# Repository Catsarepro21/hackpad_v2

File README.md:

# Macropad
A custom macropad with 6 keys, bluetooth(ESP32-S3), battery, RGB, 2 and rotary encoders. This is my second macropad, because the first one wasn't that good but I still have parts some parts left over from it. 

Files:

[PCB](PCB)

[Case](https://github.com/Catsarepro21/hackpad_v2/blob/main/case)

[Gerbers](PCB/gerbers.zip)

BOM: [BOM.md](BOM.md)

[Onshape](https://cad.onshape.com/documents/e5e00bd96b00b1f98fd3bff8/w/d80bdedc56342f5387c6fe9a/e/f05423852afba8350f5d5474?renderMode=0&uiState=6ad917cca941be13c57e1d41)

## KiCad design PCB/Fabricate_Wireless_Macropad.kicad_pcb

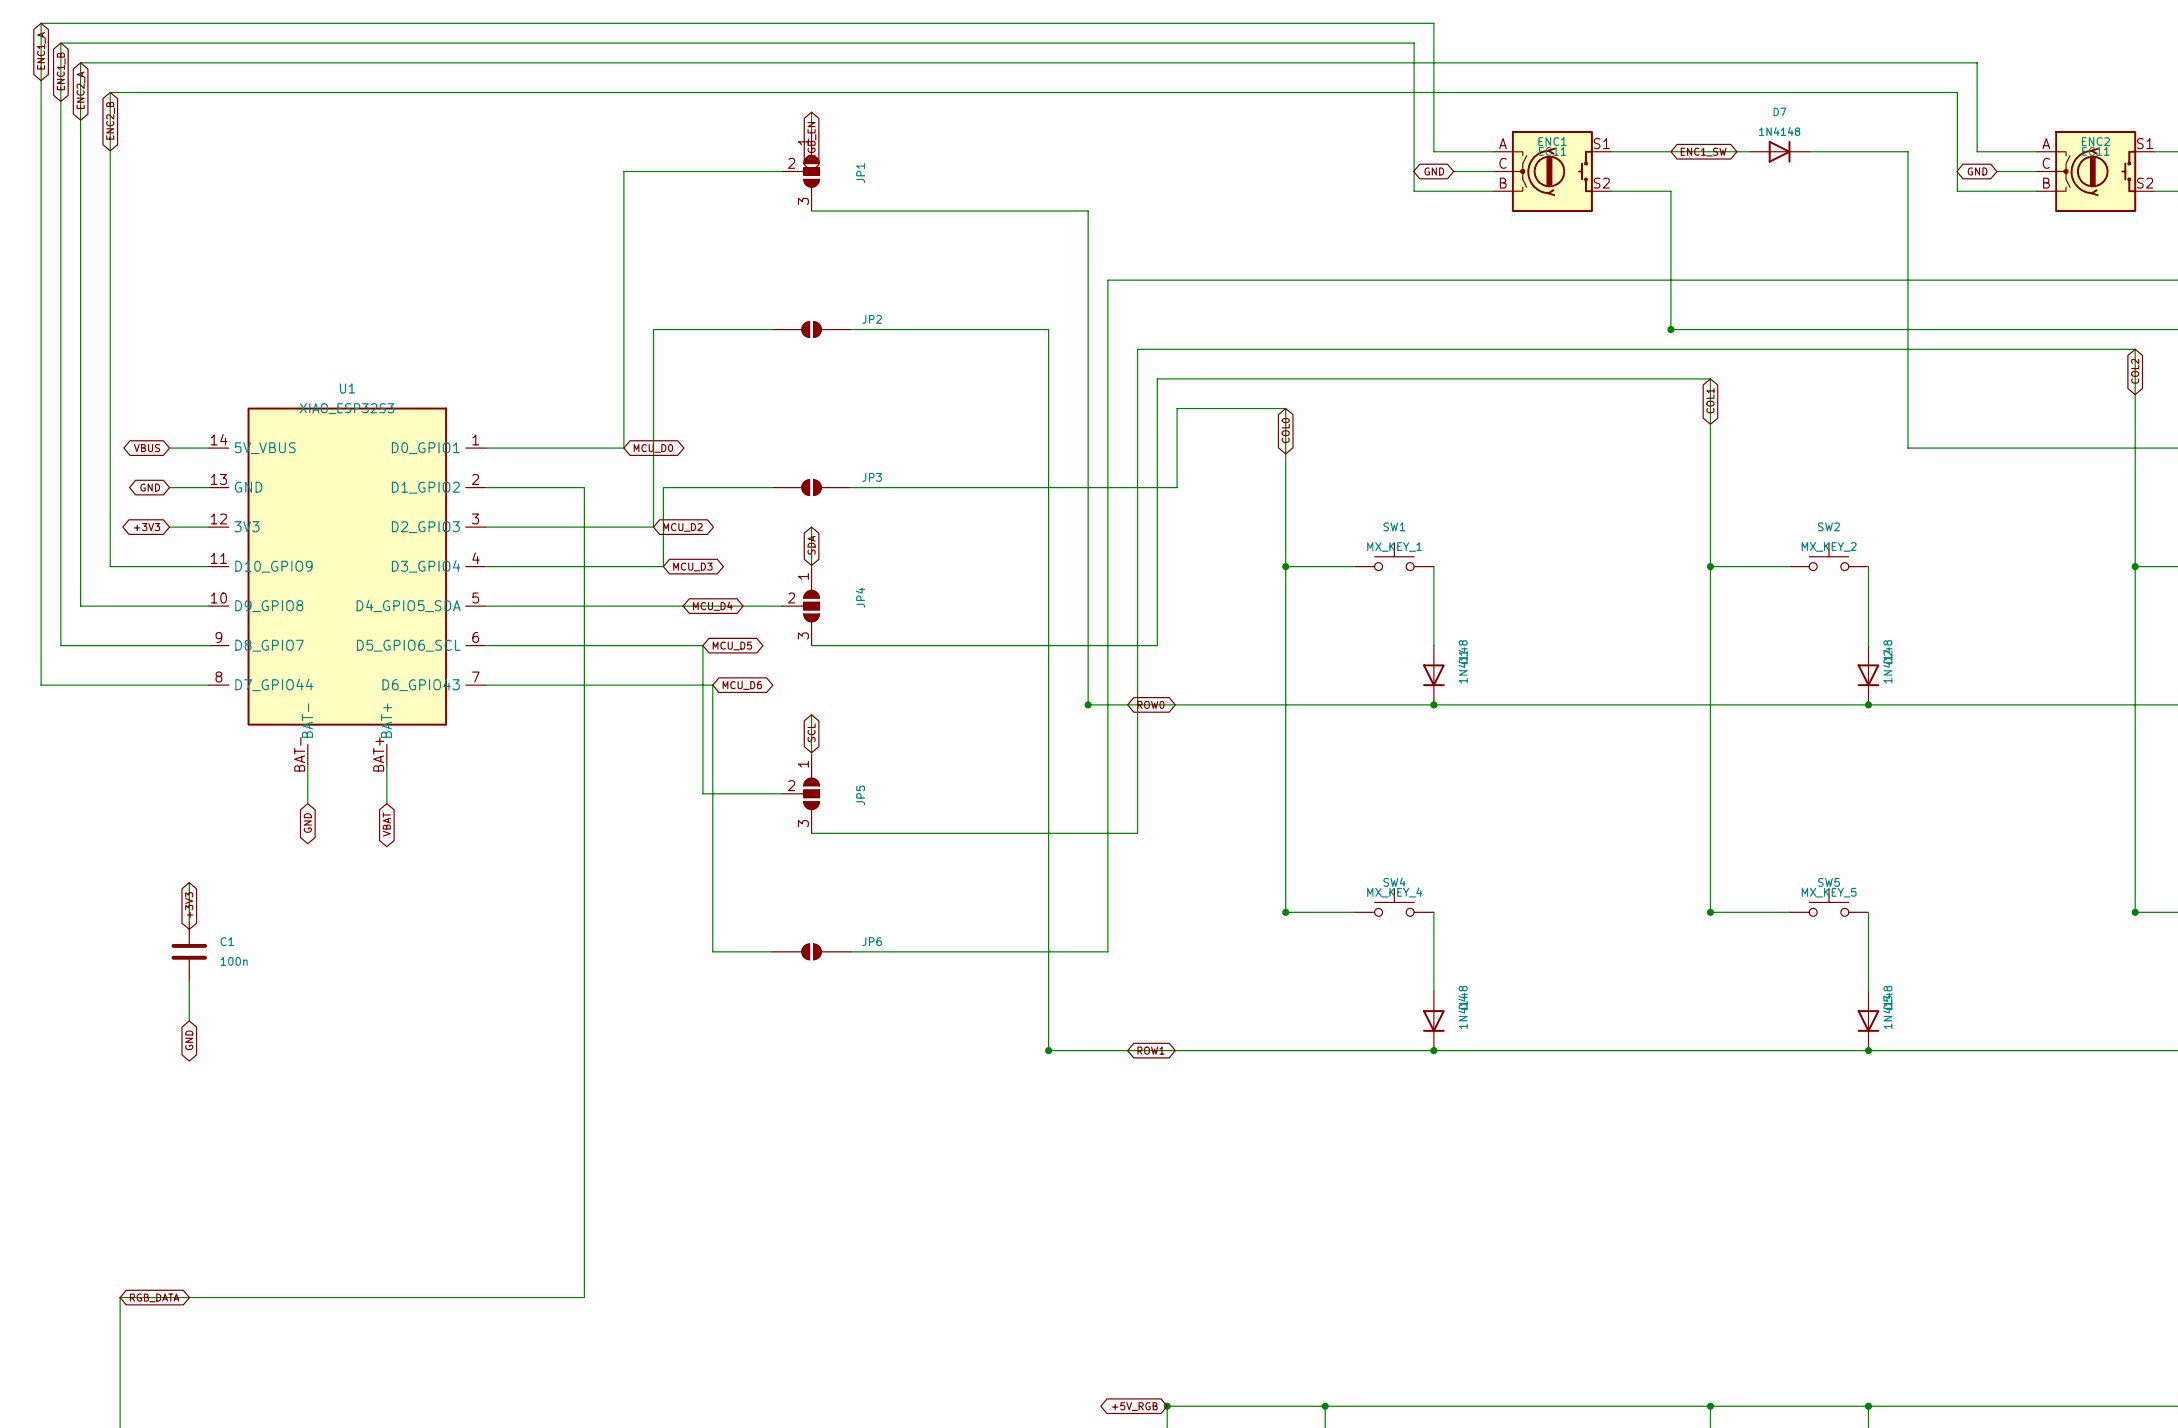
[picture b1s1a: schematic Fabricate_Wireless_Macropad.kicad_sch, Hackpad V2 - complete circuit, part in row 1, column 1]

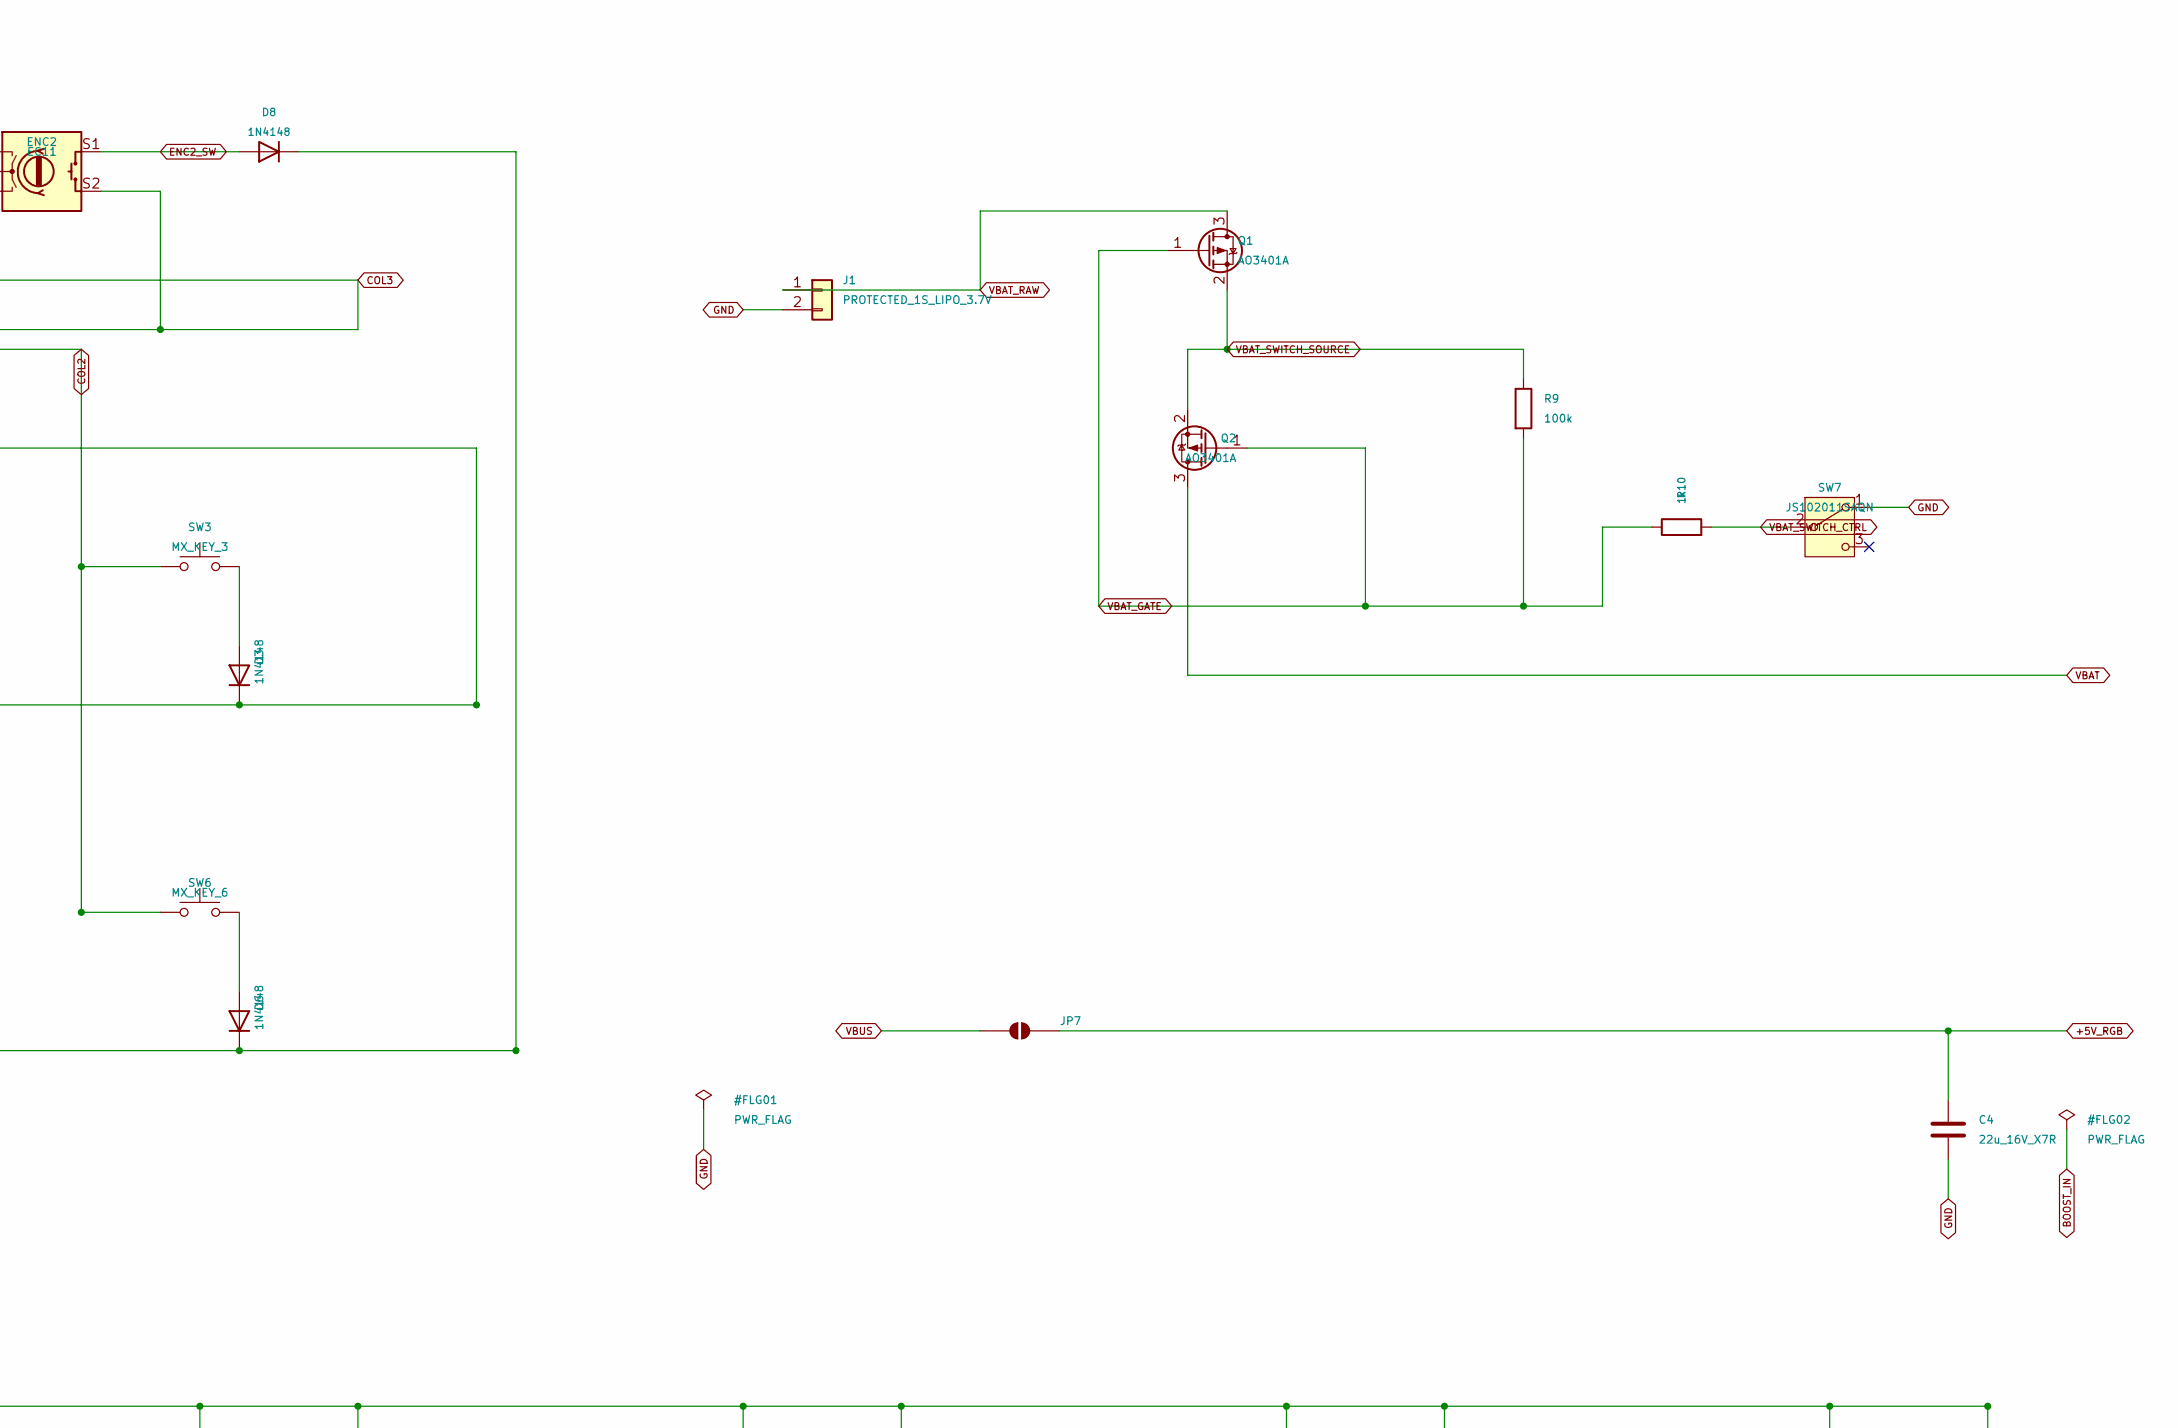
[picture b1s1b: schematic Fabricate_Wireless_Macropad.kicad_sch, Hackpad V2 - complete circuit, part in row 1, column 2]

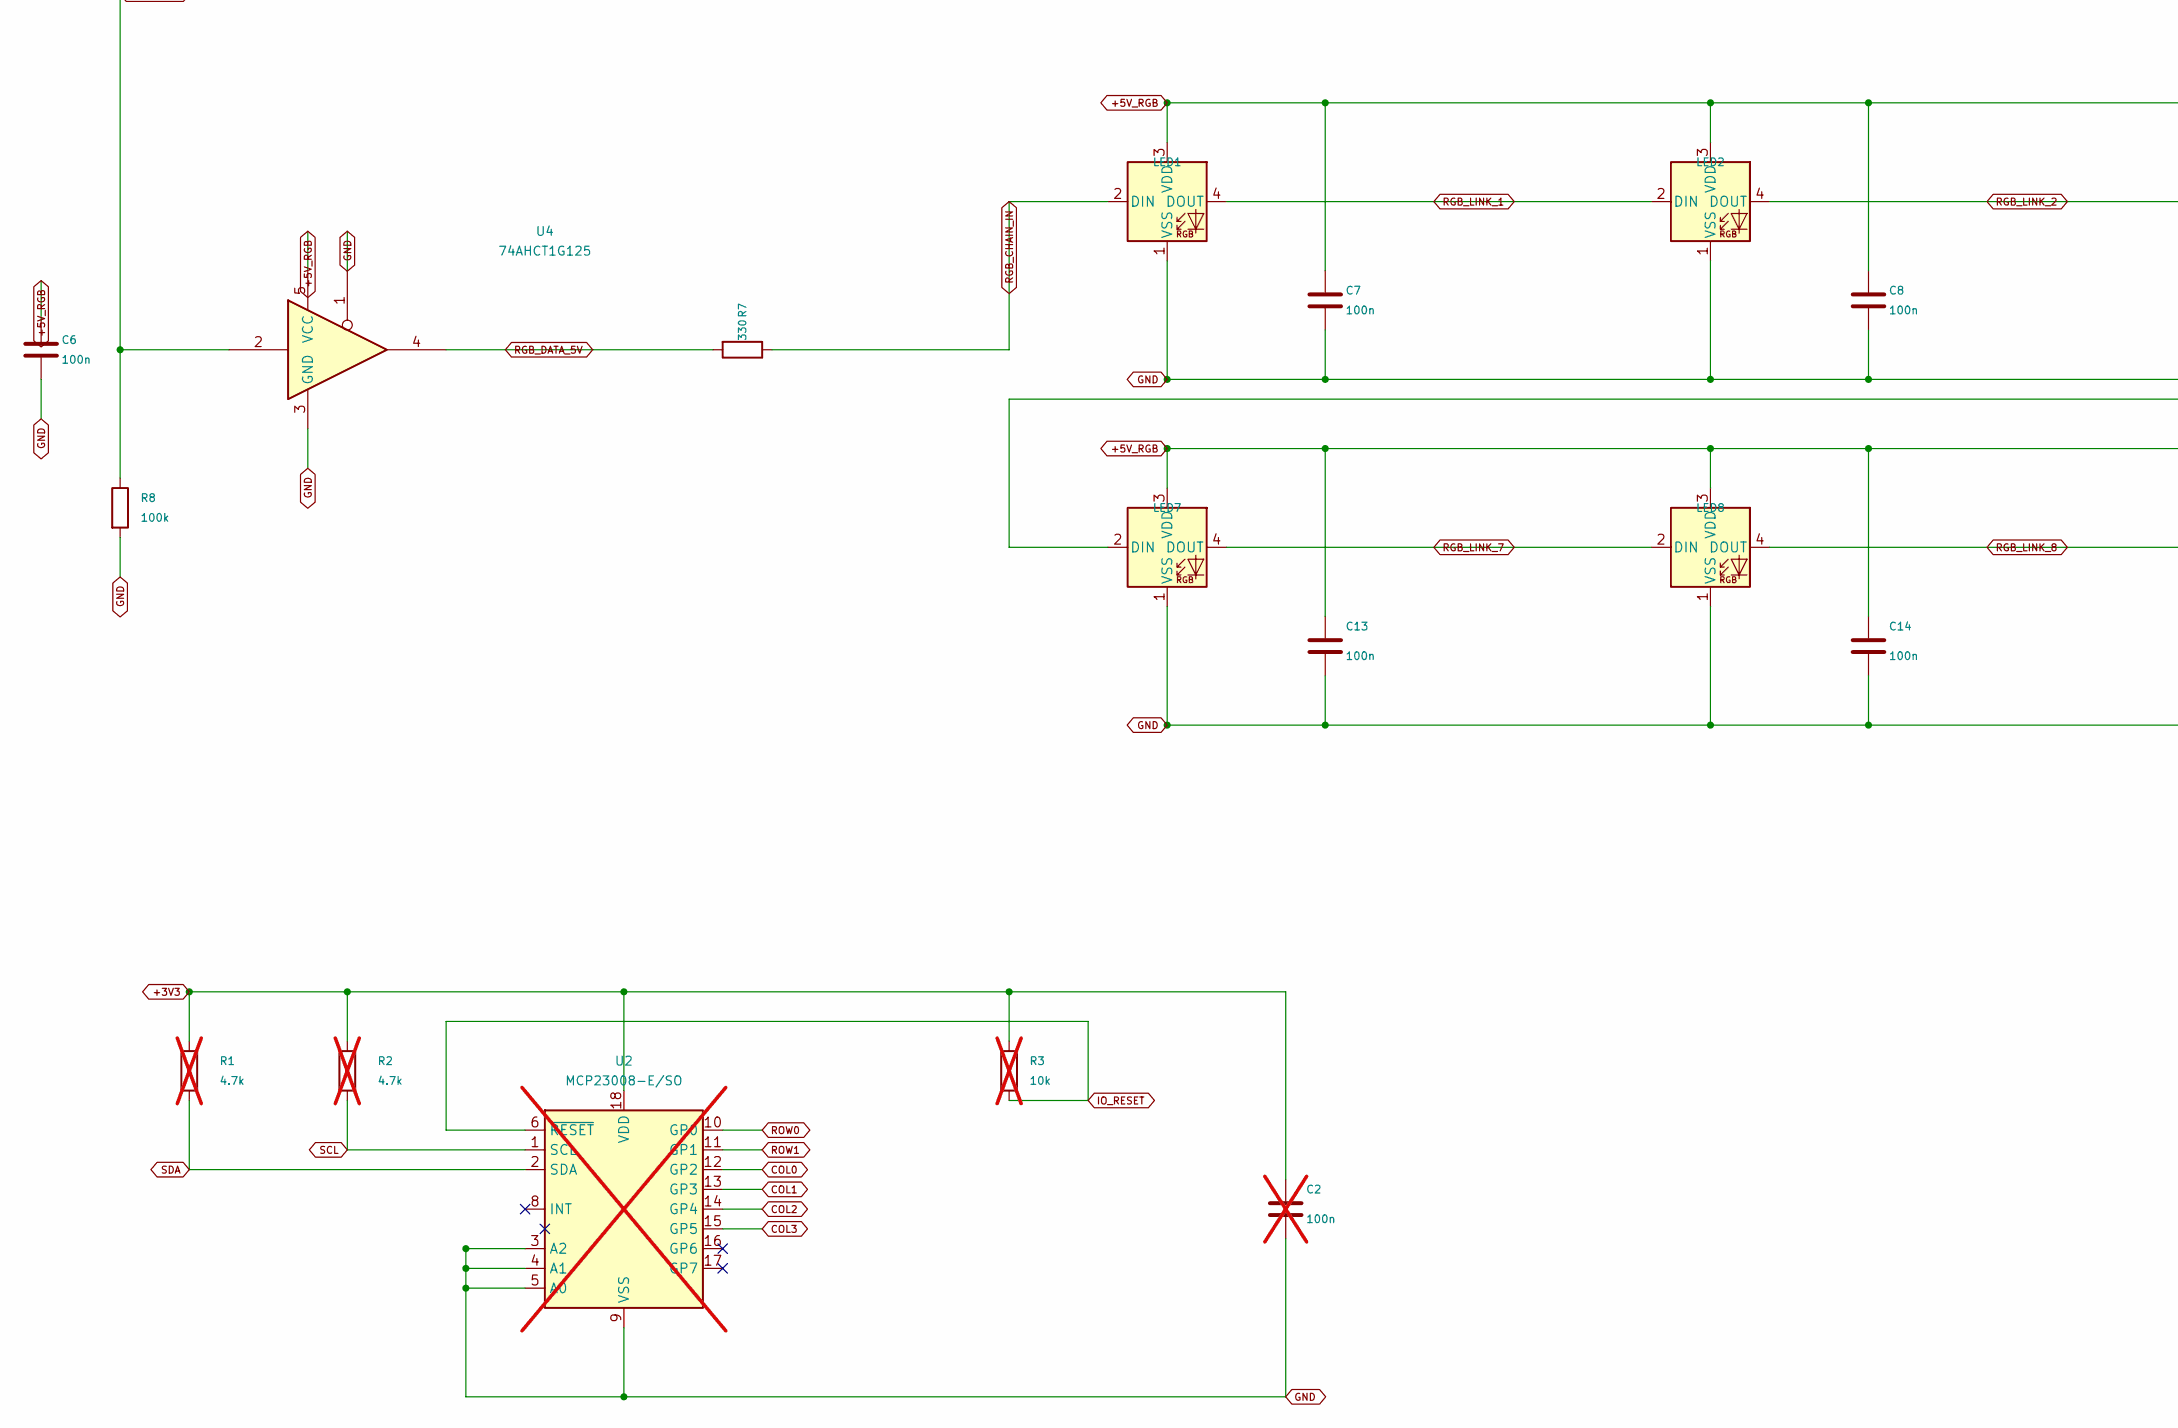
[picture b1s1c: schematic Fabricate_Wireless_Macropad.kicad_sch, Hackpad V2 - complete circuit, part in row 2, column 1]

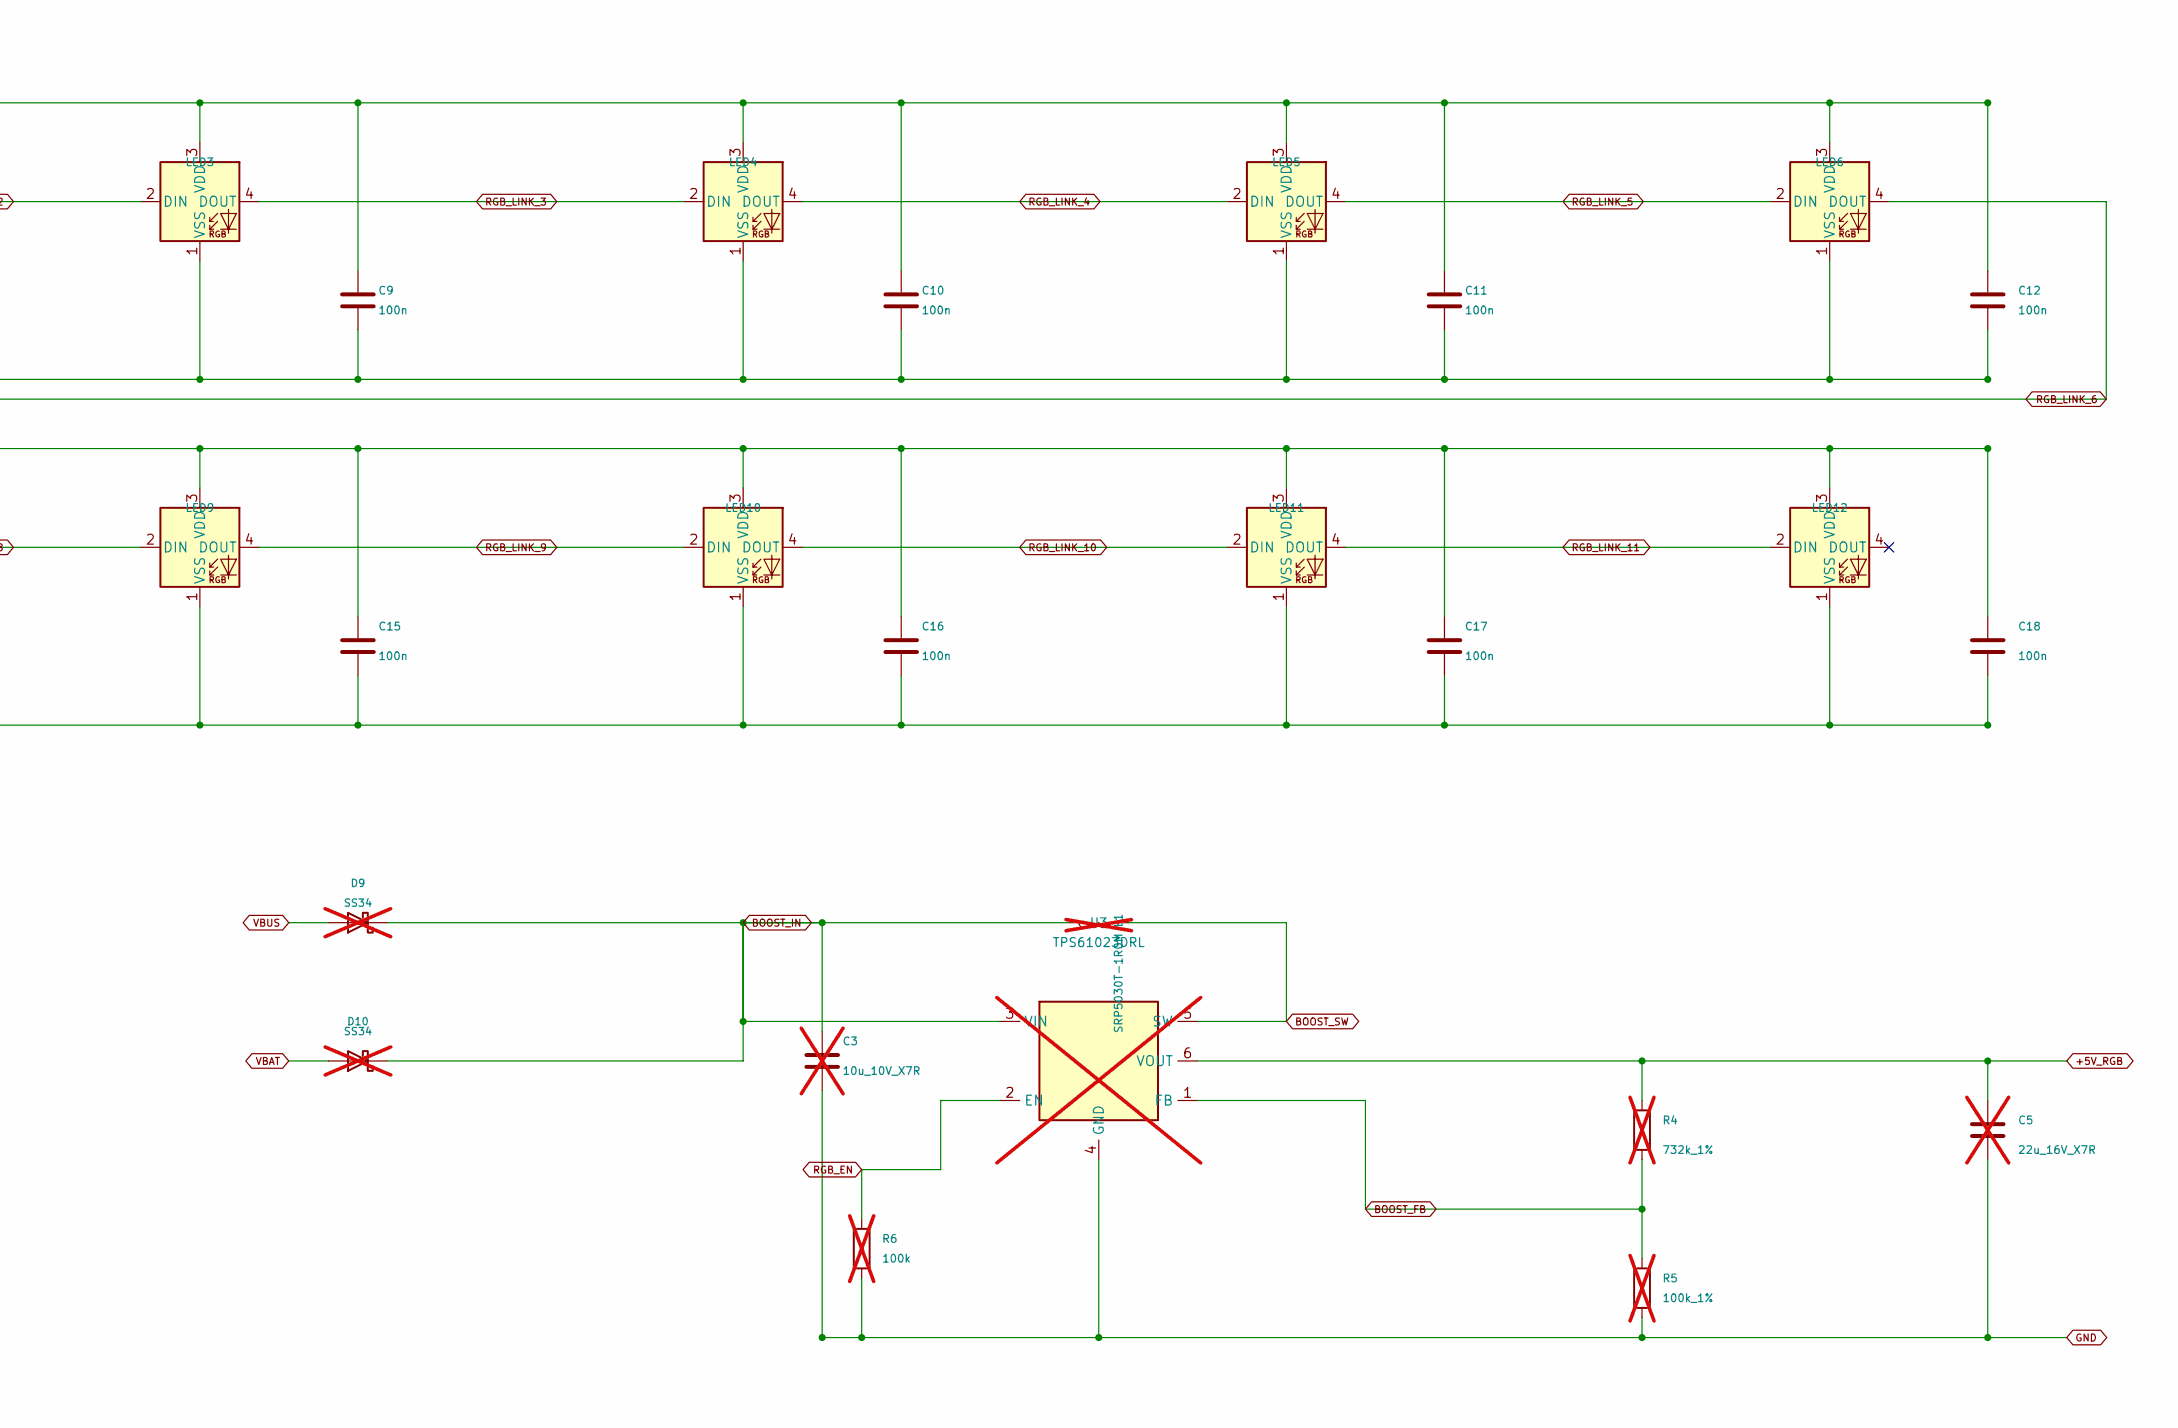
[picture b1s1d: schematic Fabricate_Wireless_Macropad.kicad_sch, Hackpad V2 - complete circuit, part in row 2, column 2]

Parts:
C1, C6, C7, C8, C9, C10, C11, C12, C13, C14, C15, C16, C17, C18: 100n; C_0805_2012Metric
C2: 100n; C_0805_2012Metric; not fitted
C3: 10u_10V_X7R; C_1206_3216Metric; MPN C1206C106K8RACTU; LCSC C2167669; not fitted
C4: 22u_16V_X7R; C_1210_3225Metric; MPN CL32B226KOJNFNE; LCSC C16196563
C5: 22u_16V_X7R; C_1210_3225Metric; MPN CL32B226KOJNFNE; LCSC C16196563; not fitted
D1, D2, D3, D4, D5, D6, D7, D8: 1N4148; D_DO-35_SOD27_P7.62mm_Horizontal
D9, D10: SS34; D_SMA; not fitted
ENC1, ENC2: EC11; RotaryEncoder_Alps_EC11E-Switch_Vertical_H20mm
J1: PROTECTED_1S_LIPO_3.7V; JST_PH_B2B-PH-K_1x02_P2.00mm_Vertical
JP1, JP4, JP5: MODE_SELECT; SolderJumper-3_P1.3mm_Open_Pad1.0x1.5mm
JP2, JP3, JP6, JP7: MODE_SELECT; SolderJumper-2_P1.3mm_Open_Pad1.0x1.5mm
L1: SRP5030T-1R0M; L_Bourns_SRP5030T; MPN SRP5030T-1R0M; not fitted
LED1: KEY_1; LED_SK6812MINI-E_3.2x2.8mm_P1.5mm_ReverseMount; MPN SK6812MINI-E
LED2: KEY_2; LED_SK6812MINI-E_3.2x2.8mm_P1.5mm_ReverseMount; MPN SK6812MINI-E
LED3: KEY_3; LED_SK6812MINI-E_3.2x2.8mm_P1.5mm_ReverseMount; MPN SK6812MINI-E
LED4: KEY_4; LED_SK6812MINI-E_3.2x2.8mm_P1.5mm_ReverseMount; MPN SK6812MINI-E
LED5: KEY_5; LED_SK6812MINI-E_3.2x2.8mm_P1.5mm_ReverseMount; MPN SK6812MINI-E
LED6: KEY_6; LED_SK6812MINI-E_3.2x2.8mm_P1.5mm_ReverseMount; MPN SK6812MINI-E
LED7: ENC_1; LED_SK6812MINI-E_3.2x2.8mm_P1.5mm_ReverseMount; MPN SK6812MINI-E
LED8: ENC_2; LED_SK6812MINI-E_3.2x2.8mm_P1.5mm_ReverseMount; MPN SK6812MINI-E
LED9: EDGE_1; LED_SK6812MINI-E_3.2x2.8mm_P1.5mm_ReverseMount; MPN SK6812MINI-E
LED10: EDGE_2; LED_SK6812MINI-E_3.2x2.8mm_P1.5mm_ReverseMount; MPN SK6812MINI-E
LED11: EDGE_3; LED_SK6812MINI-E_3.2x2.8mm_P1.5mm_ReverseMount; MPN SK6812MINI-E
LED12: EDGE_4; LED_SK6812MINI-E_3.2x2.8mm_P1.5mm_ReverseMount; MPN SK6812MINI-E
Q1, Q2: AO3401A; SOT-23
R1, R2: 4.7k; R_0805_2012Metric; not fitted
R3: 10k; R_0805_2012Metric; not fitted
R4: 732k_1%; R_0805_2012Metric; not fitted
R5: 100k_1%; R_0805_2012Metric; not fitted
R6: 100k; R_0805_2012Metric; not fitted
R7: 330; R_0805_2012Metric
R8, R9: 100k; R_0805_2012Metric
R10: 1k; R_0805_2012Metric
SW1: MX_KEY_1; SW_Cherry_MX_1.00u_PCB
SW2: MX_KEY_2; SW_Cherry_MX_1.00u_PCB
SW3: MX_KEY_3; SW_Cherry_MX_1.00u_PCB
SW4: MX_KEY_4; SW_Cherry_MX_1.00u_PCB
SW5: MX_KEY_5; SW_Cherry_MX_1.00u_PCB
SW6: MX_KEY_6; SW_Cherry_MX_1.00u_PCB
SW7: JS102011SAQN; SW_SPDT_CK_JS102011SAQN
U1: XIAO_ESP32S3; XIAO_S3_Socket_WiredBattery
U2: MCP23008-E/SO; SOIC-18W_7.5x11.6mm_P1.27mm; MPN MCP23008-E/SO; not fitted
U3: TPS61023DRL; SOT-563; not fitted
U4: 74AHCT1G125; SOT-23-5

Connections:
+3V3: C1.1, C2.1, R1.1, R2.1, R3.1, U1.12 (3V3), U2.18 (VDD)
+5V_RGB: C4.1, C5.1, C6.1, C7.1, C8.1, C9.1, C10.1, C11.1, C12.1, C13.1, C14.1, C15.1, C16.1, C17.1, C18.1, JP7.2 (B), LED1.3 (VDD), LED2.3 (VDD), LED3.3 (VDD), LED4.3 (VDD), LED5.3 (VDD), LED6.3 (VDD), LED7.3 (VDD), LED8.3 (VDD), LED9.3 (VDD), LED10.3 (VDD), LED11.3 (VDD), LED12.3 (VDD), R4.1, U3.6 (VOUT), U4.5 (VCC)
BOOST_FB: R4.2, R5.1, U3.1 (FB)
BOOST_IN: C3.1, D9.1 (K), D10.1 (K), L1.2, U3.3 (VIN)
BOOST_SW: L1.1, U3.5 (SW)
COL0: JP3.2 (B), SW1.1, SW4.1, U2.12 (GP2)
COL1: JP4.3 (B), SW2.1, SW5.1, U2.13 (GP3)
COL2: JP5.3 (B), SW3.1, SW6.1, U2.14 (GP4)
COL3: ENC1.S2, ENC2.S2, JP6.2 (B), U2.15 (GP5)
ENC1_A: ENC1.A, U1.8 (D7_GPIO44)
ENC1_B: ENC1.B, U1.9 (D8_GPIO7)
ENC1_SW: D7.2 (A), ENC1.S1
ENC2_A: ENC2.A, U1.10 (D9_GPIO8)
ENC2_B: ENC2.B, U1.11 (D10_GPIO9)
ENC2_SW: D8.2 (A), ENC2.S1
GND: C1.2, C2.2, C3.2, C4.2, C5.2, C6.2, C7.2, C8.2, C9.2, C10.2, C11.2, C12.2, C13.2, C14.2, C15.2, C16.2, C17.2, C18.2, ENC1.C, ENC2.C, J1.2, LED1.1 (VSS), LED2.1 (VSS), LED3.1 (VSS), LED4.1 (VSS), LED5.1 (VSS), LED6.1 (VSS), LED7.1 (VSS), LED8.1 (VSS), LED9.1 (VSS), LED10.1 (VSS), LED11.1 (VSS), LED12.1 (VSS), R5.2, R6.2, R8.2, SW7.1 (A), U1.13 (GND), U1.BAT-, U2.3 (A2), U2.4 (A1), U2.5 (A0), U2.9 (VSS), U3.4 (GND), U4.1, U4.3 (GND)
IO_RESET: R3.2, U2.6 (~RESET)
MCU_D0: JP1.2 (C), U1.1 (D0_GPIO1)
MCU_D2: JP2.1 (A), U1.3 (D2_GPIO3)
MCU_D3: JP3.1 (A), U1.4 (D3_GPIO4)
MCU_D4: JP4.2 (C), U1.5 (D4_GPIO5_SDA)
MCU_D5: JP5.2 (C), U1.6 (D5_GPIO6_SCL)
MCU_D6: JP6.1 (A), U1.7 (D6_GPIO43)
unnamed: D1.2 (A), SW1.2
unnamed: D2.2 (A), SW2.2
unnamed: D3.2 (A), SW3.2
unnamed: D4.2 (A), SW4.2
unnamed: D5.2 (A), SW5.2
unnamed: D6.2 (A), SW6.2
RGB_CHAIN_IN: LED1.2 (DIN), R7.1
RGB_DATA: R8.1, U1.2 (D1_GPIO2), U4.2
RGB_DATA_5V: R7.2, U4.4
RGB_EN: JP1.1 (A), R6.1, U3.2 (EN)
RGB_LINK_1: LED1.4 (DOUT), LED2.2 (DIN)
RGB_LINK_2: LED2.4 (DOUT), LED3.2 (DIN)
RGB_LINK_3: LED3.4 (DOUT), LED4.2 (DIN)
RGB_LINK_4: LED4.4 (DOUT), LED5.2 (DIN)
RGB_LINK_5: LED5.4 (DOUT), LED6.2 (DIN)
RGB_LINK_6: LED6.4 (DOUT), LED7.2 (DIN)
RGB_LINK_7: LED7.4 (DOUT), LED8.2 (DIN)
RGB_LINK_8: LED8.4 (DOUT), LED9.2 (DIN)
RGB_LINK_9: LED9.4 (DOUT), LED10.2 (DIN)
RGB_LINK_10: LED10.4 (DOUT), LED11.2 (DIN)
RGB_LINK_11: LED11.4 (DOUT), LED12.2 (DIN)
ROW0: D1.1 (K), D2.1 (K), D3.1 (K), D7.1 (K), JP1.3 (B), U2.10 (GP0)
ROW1: D4.1 (K), D5.1 (K), D6.1 (K), D8.1 (K), JP2.2 (B), U2.11 (GP1)
SCL: JP5.1 (A), R2.2, U2.1 (SCL)
SDA: JP4.1 (A), R1.2, U2.2 (SDA)
VBAT: D10.2 (A), Q2.3 (D), U1.BAT+
VBAT_GATE: Q1.1 (G), Q2.1 (G), R9.2, R10.1
VBAT_RAW: J1.1, Q1.3 (D)
VBAT_SWITCH_CTRL: R10.2, SW7.2 (B)
VBAT_SWITCH_SOURCE: Q1.2 (S), Q2.2 (S), R9.1
VBUS: D9.2 (A), JP7.1 (A), U1.14 (5V_VBUS)

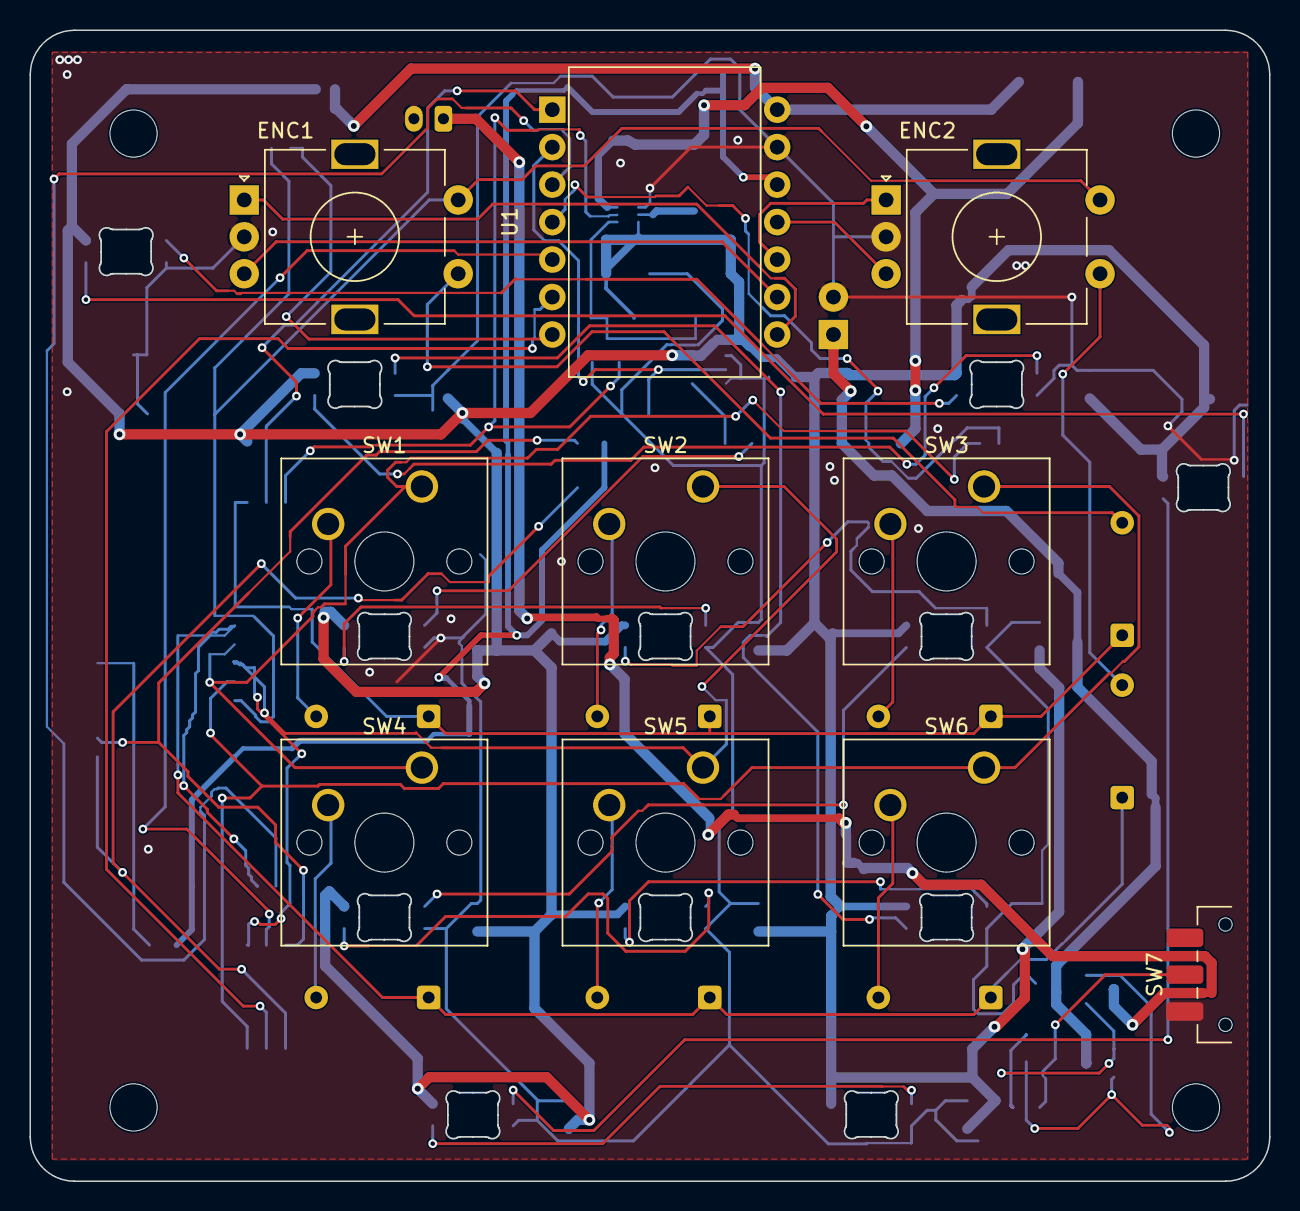
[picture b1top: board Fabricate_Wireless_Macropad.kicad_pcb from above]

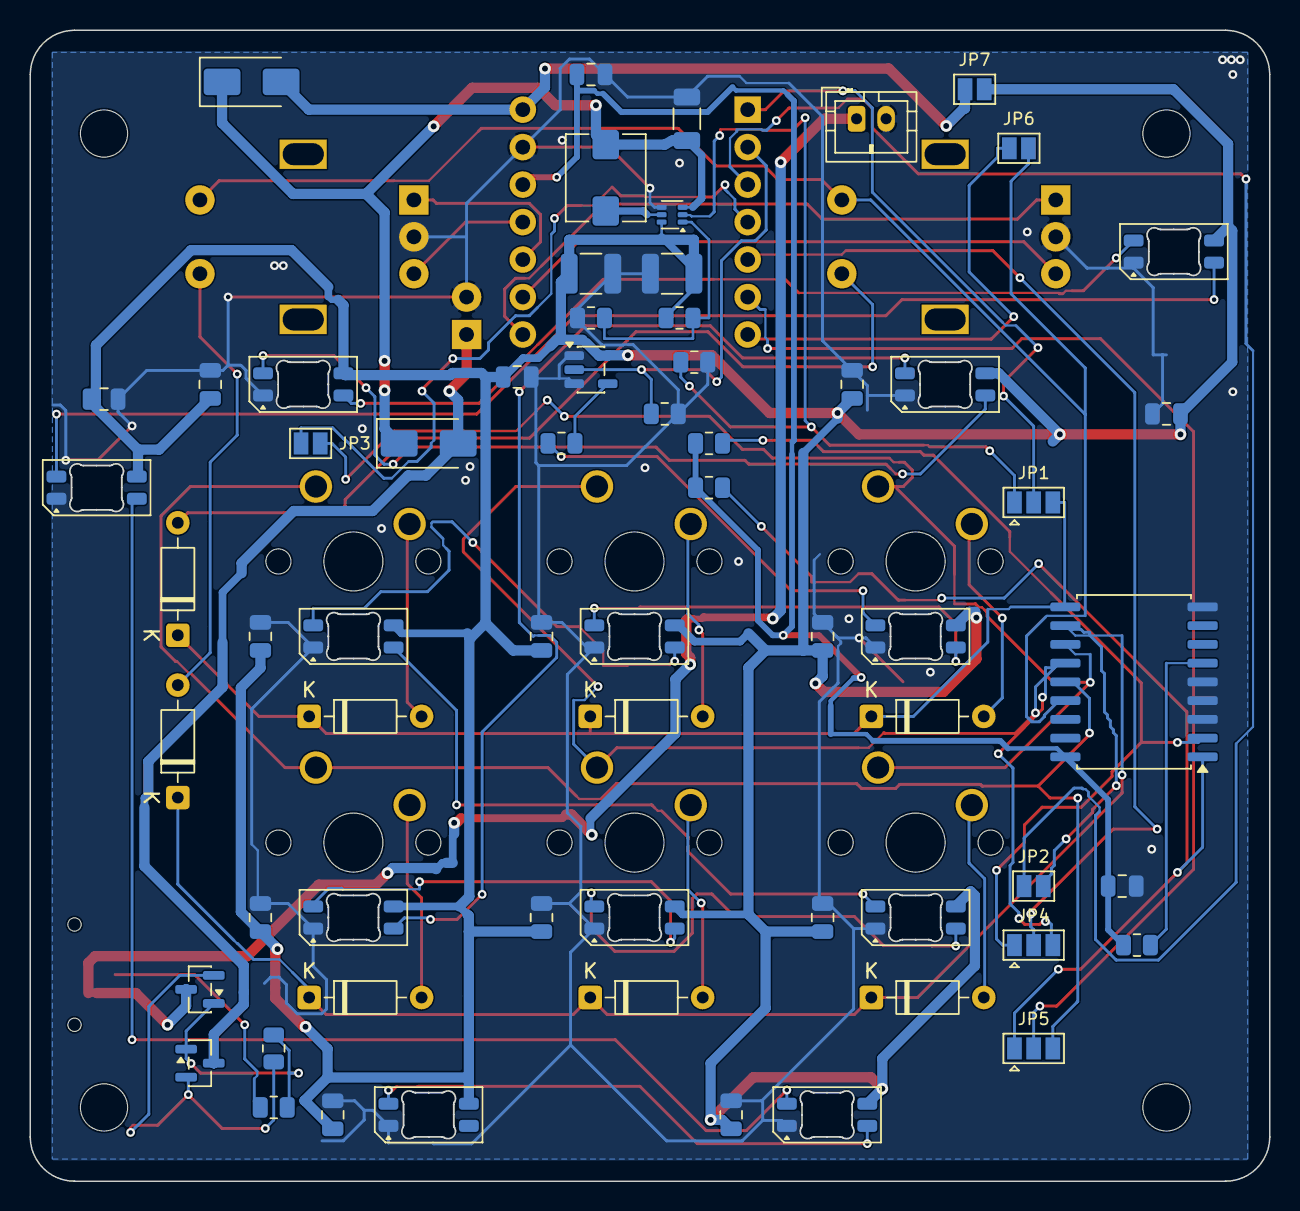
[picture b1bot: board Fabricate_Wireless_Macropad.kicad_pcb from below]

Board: 2 copper layers, 84.0 x 78.0 mm, 78 parts (64 on the bottom side), 54 nets.

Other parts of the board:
MH1, MH2, MH3, MH4: MountingHole_3.2mm_M3

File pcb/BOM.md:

# Simple build shopping list

DigiKey cart Web ID **378054863**, rebuilt and captured October 17, 2026: **$23.57 parts + $8.49 estimated ground shipping + $2.01 estimated tariffs = $34.07 before sales tax**. At that capture, all 14 lines showed Immediate availability; the cart also warns of an additional processing day. These are saved cart prices, not a refreshed checkout quote. No LCSC order is needed for this population. Do not purchase both old carts and this one.

A rough 7.25-7.5% tax allowance gives about $36.54-$36.63 if applied to the entire $34.07; actual taxable base, delivery address and checkout determine the final total. ZIP 27560 alone does not establish an exact tax quote. PCB fabrication, its delivery, case printing and consumables remain unquoted. No order placed.

| Reference/use | Part | Needed | Cart quantity | Line USD |
|---|---|---:|---:|---:|
| U1 | XIAO ESP32-S3 113991114, 1597-113991114-ND | 1 | 1 | 7.49 |
| J1 | B2B-PH-K-S, 455-1704-ND | 1 | 1 | 0.12 |
| U1 sockets | PPTC071LFBN-RC, S7005-ND | 2 | 2 | 1.16 |
| U1 male headers | Seeed 102010490 five-pack | 2 strips | 1 pack | 0.25 |
| U4 | SN74AHCT1G125DBVR, 296-4708-1-ND | 1 | 1 | 0.14 |
| R8,R9 | RC0805FR-07100KL, 311-100KCRCT-ND | 2 | 10 | 0.36 |
| R7 | RC0805FR-07330RL, 311-330CRCT-ND | 1 | 1 | 0.10 |
| R10 | RC0805FR-071KL, 311-1.00KCRCT-ND | 1 | 1 | 0.10 |
| Battery pad leads | Adafruit 1954 wire pack, 1528-1964-ND | 1 pair | 1 pack | 1.95 |
| Q1,Q2 | AO3401A, 785-1001-1-ND | 2 | 2 | 1.04 |
| C1,C6-C18 | CC0805KRX7R9BB104 100nF 50V X7R 0805, 311-1140-1-ND | 14 | 14 | 1.37 |
| C4 | CL32B226KOJNNNE 22uF 16V X7R 1210, 1276-1855-1-ND | 1 | 1 | 0.64 |
| SW7 | JS102011SAQN, 401-1999-1-ND | 1 | 1 | 0.90 |
| Battery | Adafruit 1578 protected 500mAh, 1528-1841-ND | 1 | 1 | 7.95 |

Use the PCB-mounted C&K SW7. The earlier remote SK12D07 switch plan is superseded. Verify JST polarity before connecting the battery. The 500mAh battery measures 29x36x4.75mm and is rated 500mA maximum continuous discharge; this build reserves battery power for the controller, not LEDs. It has less runtime than the earlier 1200mAh option. The XIAO provides charging; no separate charger is needed.

Owned: six MX switches, six DSA keycaps, eight 1N4148 diodes, two EC11 encoders with clicks, twelve SK6812 MINI-E LEDs, four M3x16 screws, four 5mm OD x 4mm heat-set inserts. Solder bridges cost no extra components. Salvaged parts have not been electrically qualified.

Optional later: U2 MCP23008-E/SO; R1/R2 4.7k; R3 10k; C2 100nF; U3 TPS61023DRLR; L1 SRP5030T-1R0M; D9/D10 B340A-13-F; C3 C1206C106K8RACTU 10uF; C5 CL32B226KOJNNNE 22uF; R4 732k; R5/R6 100k. All corresponding footprints remain on the PCB. See [build instructions](Build-options.md) before populating them.

[Shared rebuilt cart](https://www.digikey.com/short/m3zh375z) · [Battery specifications](https://www.adafruit.com/product/1578) · [Battery datasheet](https://cdn-shop.adafruit.com/product-files/1578/Datasheet.pdf)

## Assembly coverage

[BOM.csv](BOM.csv) contains the 14 priced shopping lines only. The tables below complete the PCB population list; owned and DNP parts do not add to the shopping subtotal. There are 78 PCB references: 53 populated components, 14 DNP components, 7 solder jumpers and 4 mounting holes.

| PCB references | Qty | Use now | Package / requirement |
|---|---:|---|---|
| SW1-SW6 | 6 | Owned MX switches | Soldered PCB-mount MX; actual plate fit still needs checking |
| ENC1,ENC2 | 2 | Owned EC11 encoders with clicks | Match the Alps EC11E switch footprint and shaft dimensions; owned exact model not documented |
| D1-D8 | 8 | Owned 1N4148 | Axial DO-35, 7.62 mm lead pitch; observe cathode markings |
| LED1-LED12 | 12 | Owned SK6812 MINI-E | 3.2 x 2.8 mm reverse-mount; observe pin 1 and PCB apertures |
| JP1-JP7 | 7 | Solder only | Configure exactly as in the build instructions; no purchased jumper parts |
| MH1-MH4 | 4 | Mounting holes | Four owned M3x16 screws and four owned 5 mm OD x 4 mm inserts |

Other assembly items: six owned DSA keycaps, one fabricated 84 x 78 mm two-layer 1.6 mm PCB, and the printed base/plate. USB-C data cable, solder, insulation and battery restraint are not priced or assumed owned. Use the antenna supplied with XIAO 113991114; its routing/placement still needs assembly verification.

## Optional footprint population - do not buy for the simple build

| References | Qty | Part/value | PCB package |
|---|---:|---|---|
| U2 | 1 | MCP23008-E/SO | Wide SOIC-18, 7.5 x 11.6 mm, 1.27 mm pitch |
| U3 | 1 | TPS61023DRLR | SOT-563 |
| L1 | 1 | SRP5030T-1R0M | Bourns SRP5030T |
| D9,D10 | 2 | B340A-13-F, SS34 equivalent specified by original BOM | SMA |
| R1,R2 | 2 | 4.7k | 0805 |
| R3 | 1 | 10k | 0805 |
| R4 | 1 | 732k, 1% | 0805 |
| R5,R6 | 2 | 100k, 1% | 0805 |
| C2 | 1 | 100nF | 0805 |
| C3 | 1 | C1206C106K8RACTU, 10uF 10V X7R | 1206 |
| C5 | 1 | CL32B226KOJNNNE, 22uF 16V X7R | 1210 |

## Assembly details and remaining checks

The two U1 sockets are 7-way, 2.54 mm pitch PPTC071LFBN-RC. The male-header pack is Seeed 102010490 (DigiKey 1597-102010490-ND), containing five 7-pin strips; two strips are needed. The manufacturer drawing gives 8.50 mm socket insulation height (the catalog rounds this to 8.51 mm). The corrected CAD represents a nominal 11.04 mm gap from carrier-board top to XIAO PCB underside: 8.50 mm socket housing plus an assumed 2.54 mm male-header plastic height. The male-header height and final seating have not been verified for the exact purchased strip. Confirm actual module height, secure mating and USB plug/cable clearance in the first assembly before printing a final case batch; the nominal envelope does not qualify the exact mated connector stack. Solder the two battery leads directly between XIAO BAT pads and the labeled carrier BAT+/BAT- pads; Adafruit 1954 supplies 20 wires, so cut and strip two suitable leads rather than relying on loose jumper contacts for battery power.

The battery is protected Adafruit 1578, with a JST-PH plug matching the 2 mm J1 connector family; measure connector polarity before connection. Switch ON to charge. RGB remains USB-only. Read the [release audit](../docs/Release-audit.md) before treating this as a tested production assembly; firmware/direct-matrix scanning, MX plate fit and powered operation remain unverified.

Source checks, October 17, 2026: [socket dimensions and pitch](https://www.digikey.com/en/products/detail/sullins-connector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, [Seeed module specification and supplied antenna](https://mm.digikey.com/Volume0/opasdata/d220001/medias/docus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, [wire pack contents](https://www.adafruit.com/product/1954), [protected battery dimensions](https://www.adafruit.com/product/1578). The rebuilt October 17 cart establishes the listed prices; current stock, shipping, tariffs and tax must be reconfirmed at checkout.

R8/R9 order quantity: two are installed; the rebuilt October 17 cart correctly orders ten for $0.36 (eight spares). The older cart's inconsistent quantity field is superseded. The saved $34.07 estimate is before tax and must be refreshed at checkout.
